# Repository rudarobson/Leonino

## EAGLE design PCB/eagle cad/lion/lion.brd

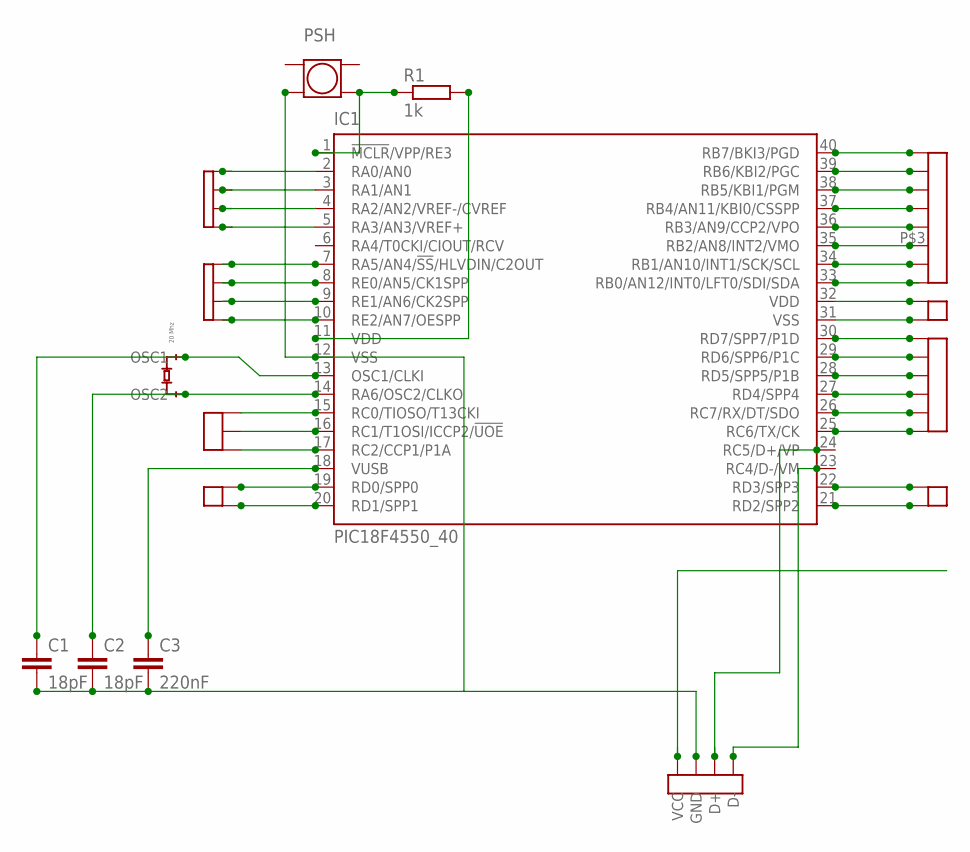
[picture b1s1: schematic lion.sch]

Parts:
BUTTON1: PUSHBTN
C1, C2: 18pF; C025-025X050
C3: 220nF; C025-025X050
IC1: PIC18F4550_40; DIL40
R1: 1k; 0204/5
U$1: USBMINIB
U$2: 20 Mhz; CRYSTAL
U$3: DUBOX3
U$4: DUBOX6
U$5: DUBOX8
U$6, U$7, U$8: DUBOX2
U$9, U$10: DUBOX4

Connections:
unnamed: C3.1, IC1.18 (VUSB)
unnamed: C1.1, IC1.13 (OSC1/CLKI), U$2.P$1 (OSC1)
unnamed: C2.1, IC1.14 (RA6/OSC2/CLKO), U$2.P$2 (OSC2)
unnamed: BUTTON1.P$2 (P12), C1.2, C2.2, C3.2, IC1.12 (VSS), U$1.GND
unnamed: BUTTON1.P$4 (P22), IC1.1 (!MCLR!/VPP/RE3), R1.1
unnamed: IC1.11 (VDD), R1.2
unnamed: IC1.2 (RA0/AN0), U$9.P$1 (P1)
unnamed: IC1.3 (RA1/AN1), U$9.P$2 (P2)
unnamed: IC1.4 (RA2/AN2/VREF-/CVREF), U$9.P$3 (P3)
unnamed: IC1.19 (RD0/SPP0), U$6.P$1 (P1)
unnamed: IC1.5 (RA3/AN3/VREF+), U$9.P$4 (P4)
unnamed: IC1.7 (RA5/AN4/!SS!/HLVDIN/C2OUT), U$10.P$1 (P1)
unnamed: IC1.8 (RE0/AN5/CK1SPP), U$10.P$2 (P2)
unnamed: IC1.9 (RE1/AN6/CK2SPP), U$10.P$3 (P3)
unnamed: IC1.10 (RE2/AN7/OESPP), U$10.P$4 (P4)
unnamed: IC1.40 (RB7/BKI3/PGD), U$5.P$8
unnamed: IC1.39 (RB6/KBI2/PGC), U$5.P$7
unnamed: IC1.38 (RB5/KBI1/PGM), U$5.P$6
unnamed: IC1.37 (RB4/AN11/KBI0/CSSPP), U$5.P$5
unnamed: IC1.36 (RB3/AN9/CCP2/VPO), U$5.P$4
unnamed: IC1.35 (RB2/AN8/INT2/VMO), U$5.P$3
unnamed: IC1.34 (RB1/AN10/INT1/SCK/SCL), U$5.P$2
unnamed: IC1.33 (RB0/AN12/INT0/LFT0/SDI/SDA), U$5.P$1
unnamed: IC1.30 (RD7/SPP7/P1D), U$4.P$6
unnamed: IC1.29 (RD6/SPP6/P1C), U$4.P$5
unnamed: IC1.28 (RD5/SPP5/P1B), U$4.P$4
unnamed: IC1.32 (VDD), U$7.P$2 (P2)
unnamed: IC1.26 (RC7/RX/DT/SDO), U$4.P$2
unnamed: IC1.25 (RC6/TX/CK), U$4.P$1
unnamed: IC1.20 (RD1/SPP1), U$6.P$2 (P2)
unnamed: IC1.31 (VSS), U$7.P$1 (P1)
unnamed: IC1.27 (RD4/SPP4), U$4.P$3
unnamed: IC1.22 (RD3/SPP3), U$8.P$2 (P2)
unnamed: IC1.17 (RC2/CCP1/P1A), U$3.P$3
unnamed: IC1.16 (RC1/T1OSI/ICCP2/!UOE), U$3.P$2
unnamed: IC1.15 (RC0/TIOSO/T13CKI), U$3.P$1
unnamed: IC1.21 (RD2/SPP2), U$8.P$1 (P1)

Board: 2 copper layers, 16 parts (0 on the bottom side), 37 nets, no tracks yet.

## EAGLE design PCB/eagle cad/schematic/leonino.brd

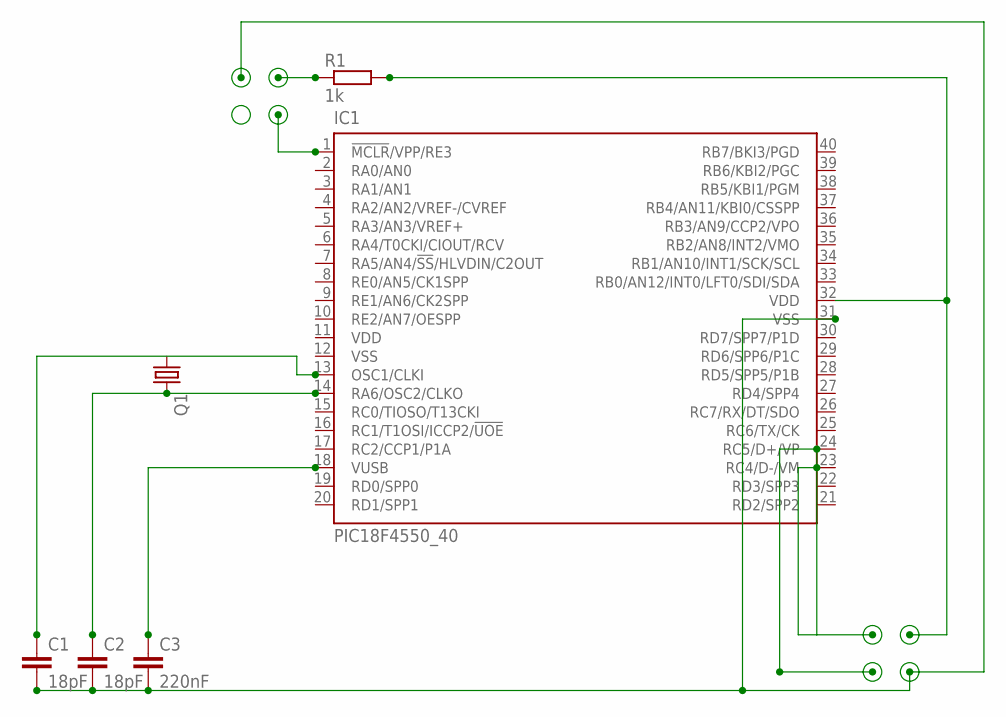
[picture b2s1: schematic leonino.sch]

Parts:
C1, C2: 18pF; C025-025X050
C3: 220nF; C025-025X050
IC1: PIC18F4550_40; DIL40
Q1: CRYSTALHC49S; HC49/S
R1: 1k; 0204/5

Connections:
unnamed: IC1.32 (VDD), R1.2
unnamed: C3.1, IC1.18 (VUSB)
unnamed: C1.1, IC1.13 (OSC1/CLKI)
unnamed: C2.1, IC1.14 (RA6/OSC2/CLKO), Q1.2
unnamed: C1.2, C2.2, C3.2, IC1.31 (VSS)
VDD: IC1.11 (VDD)
VSS: IC1.12 (VSS)

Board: 2 copper layers, 6 parts (0 on the bottom side), 5 nets, no tracks yet.

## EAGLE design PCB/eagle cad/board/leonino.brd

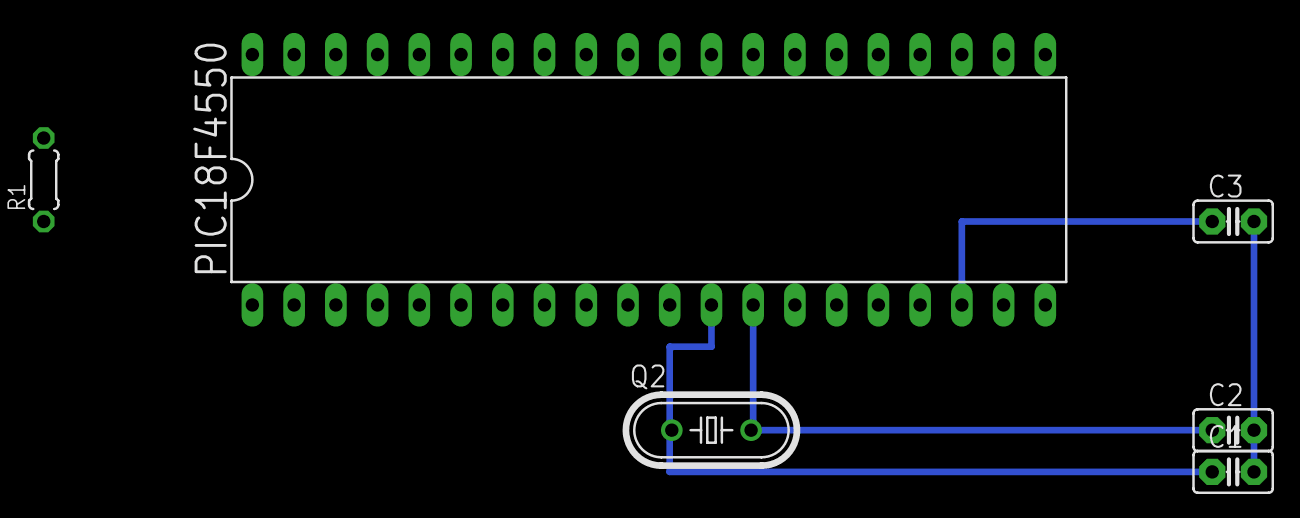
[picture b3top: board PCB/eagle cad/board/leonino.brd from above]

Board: 2 copper layers, 6 parts (0 on the bottom side), 3 nets.

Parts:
C1, C2: 18pF; C2.5-2
C3: 220nF; C2.5-2
PIC18F4550: DIL40
Q2: 20MHZ; HC49/S
R1: 0204/5

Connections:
S$1: C2.1, PIC18F4550.13
S$3: C3.1, PIC18F4550.18
S$4: C1.2, C2.2, C3.2

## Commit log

2013-08-26 Leonin first sync
2013-08-26 Leonino reorganized
2013-08-27 Bugs Fixeds
    USB Stack bugs fixeds and adapted to work with XC8, #warning added and
    should remain until XC8 becomes better
2013-08-31 code cleanup
2013-08-31 Bootloader Stable but Large
    More readable code
    Address come in little Endian
2013-09-01 Bootloader seems to be done
    old driver removed
2013-09-09 New Project
    Starting IDE in Java
    using Java to communicate with USB (only works at x86 JVM)
2013-09-10 IDE started working
2013-09-11 IDE upgraded
    Problem for uploading in Java
2013-09-11 Bootloader Working
    Wrong comment on previous commit
2013-09-18 PCB updated
